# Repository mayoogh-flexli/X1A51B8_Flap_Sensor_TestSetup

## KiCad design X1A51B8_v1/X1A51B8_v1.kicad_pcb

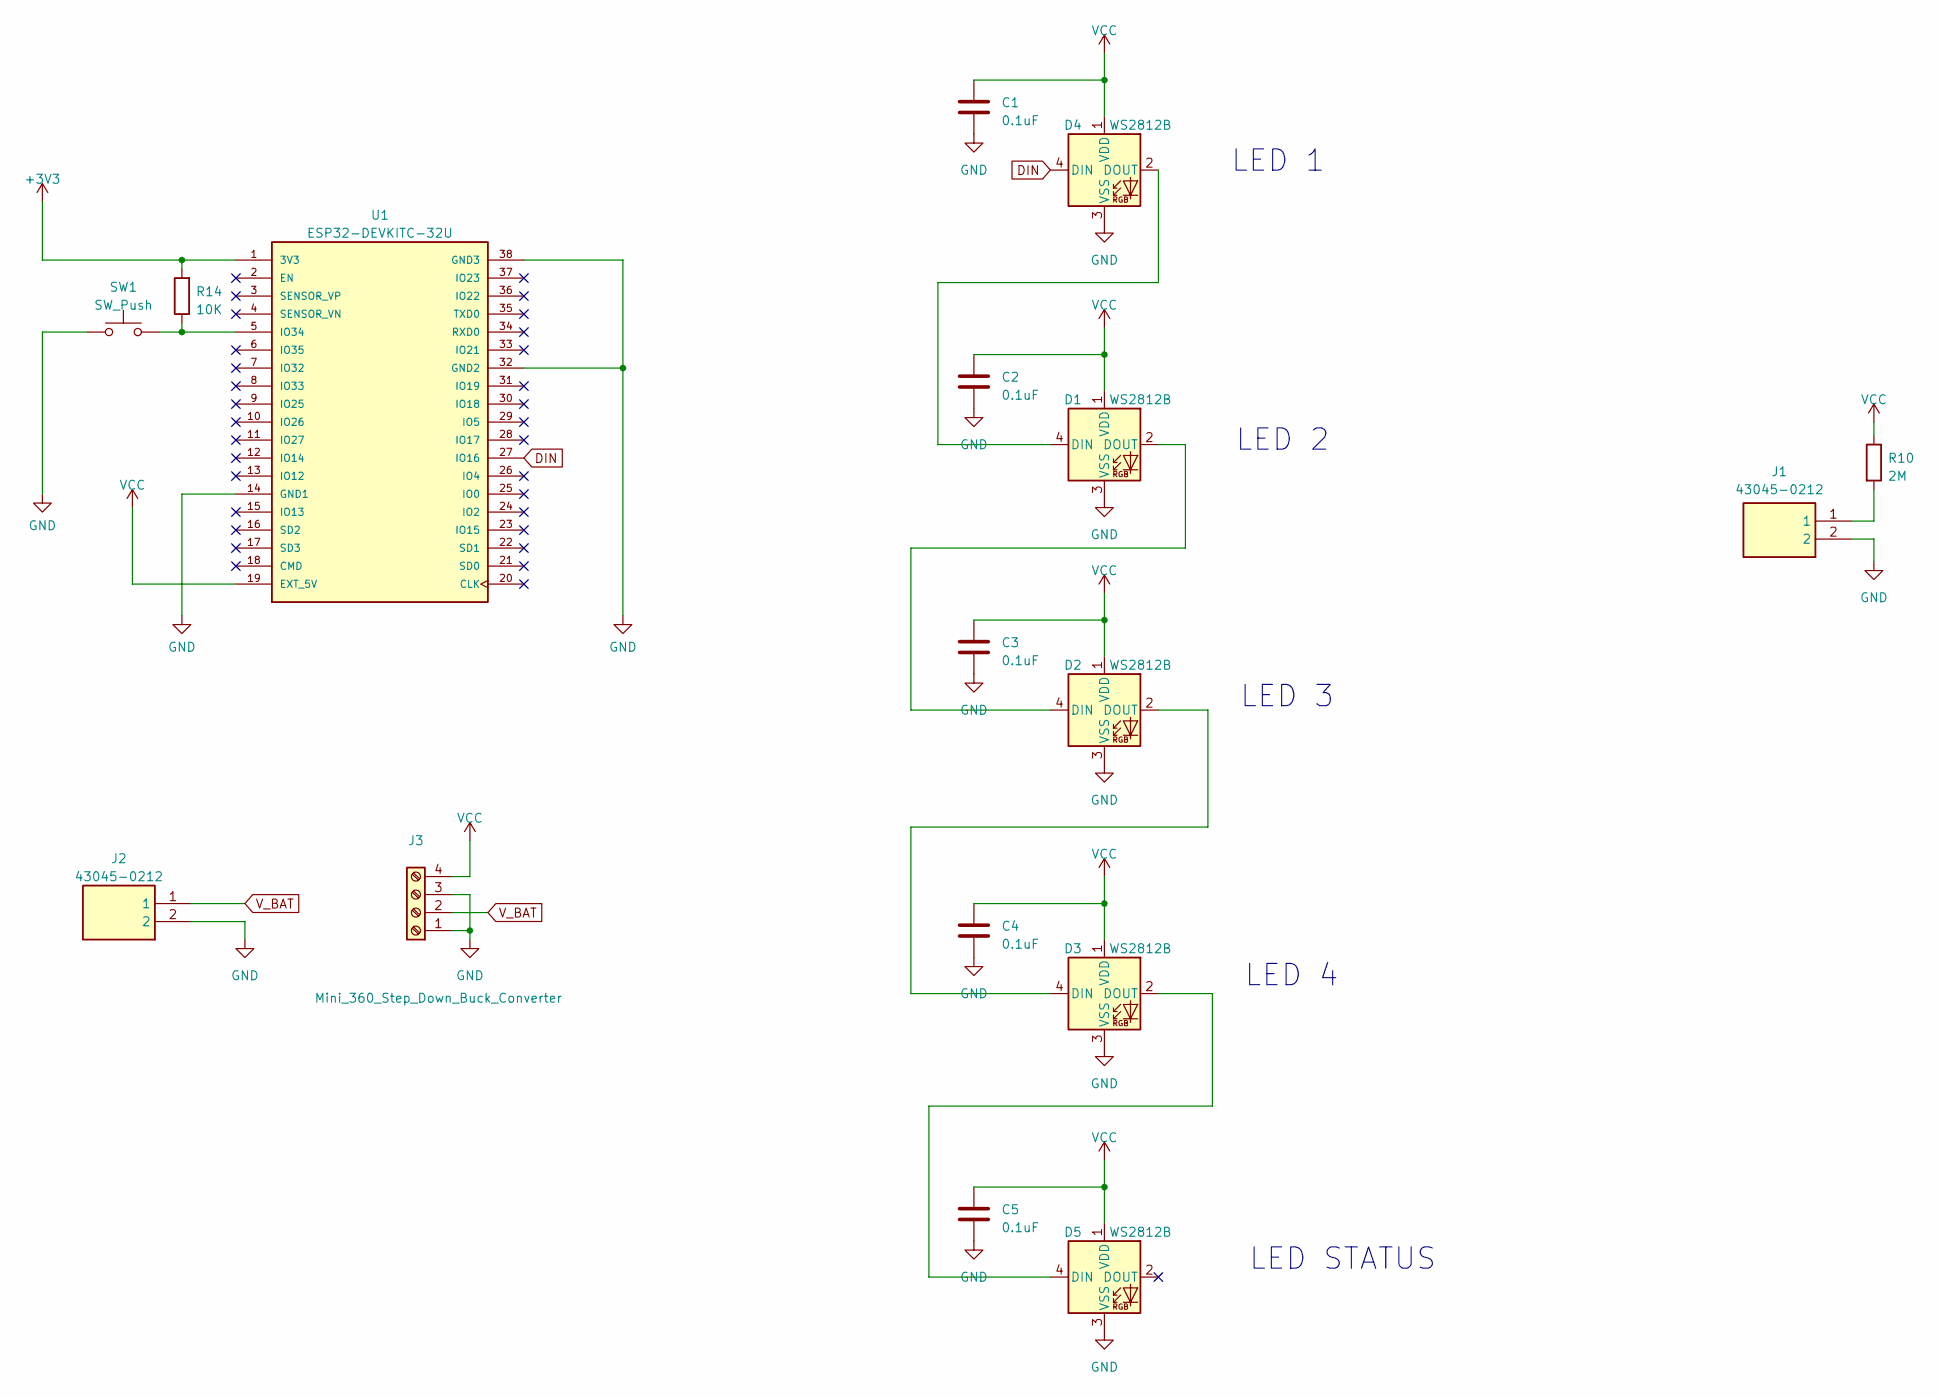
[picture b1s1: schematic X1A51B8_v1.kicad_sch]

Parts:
C1, C2, C3, C4, C5: 0.1uF; C_0805_2012Metric_Pad1.18x1.45mm_HandSolder
D1, D2, D3, D4, D5: WS2812B; LED_WS2812B_PLCC4_5.0x5.0mm_P3.2mm
J1, J2: 43045-0212; 43045-02xx_121314
J3: Mini_360_Step_Down_Buck_Converter; PinHeader_1x04_P2.54mm_Vertical
R10: 2M; R_0805_2012Metric
R14: 10K; R_0805_2012Metric
SW1: SW_Push; SW_PUSH_6mm
U1: ESP32-DEVKITC-32U; MODULE_ESP32-DEVKITC-32U; PARTREV N/A

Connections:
+3V3: R14.2, U1.1 (3V3)
DIN: D4.4 (DIN), U1.27 (IO16)
GND: C1.2, C2.2, C3.2, C4.2, C5.2, D1.3 (VSS), D2.3 (VSS), D3.3 (VSS), D4.3 (VSS), D5.3 (VSS), J1.2, J2.2, J3.1, J3.3, SW1.1, U1.14 (GND1), U1.32 (GND2), U1.38 (GND3)
unnamed: D1.4 (DIN), D4.2 (DOUT)
unnamed: D1.2 (DOUT), D2.4 (DIN)
unnamed: D2.2 (DOUT), D3.4 (DIN)
unnamed: D3.2 (DOUT), D5.4 (DIN)
unnamed: J1.1, R10.2
unnamed: R14.1, SW1.2, U1.5 (IO34)
VCC: C1.1, C2.1, C3.1, C4.1, C5.1, D1.1 (VDD), D2.1 (VDD), D3.1 (VDD), D4.1 (VDD), D5.1 (VDD), J3.4, R10.1, U1.19 (EXT_5V)
V_BAT: J2.1, J3.2

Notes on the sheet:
LED 1
LED STATUS
LED 3
LED 4
LED 2

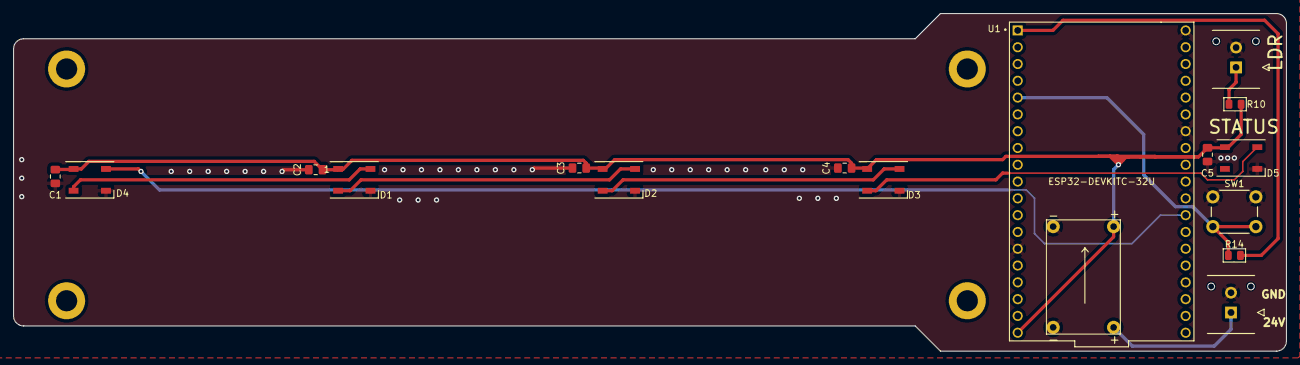
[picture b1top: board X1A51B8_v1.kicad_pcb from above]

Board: 2 copper layers, 192.5 x 51.1 mm, 17 parts (0 on the bottom side), 11 nets.
